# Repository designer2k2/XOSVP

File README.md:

# Xbox Open Source Video Project

XOSVP is an open-source alternative to the Microsoft HD AV Pack. The XOSVP strives to produce the absolute best analog video quality out of your original Xbox.

## Features
- Highest possible quality analog Y/Pb/Pr component video out
    - Impedance matched board traces and cabling from original Xbox
    - High quality video filter + amplifier, [THS7316](https://www.ti.com/lit/ds/symlink/ths7316.pdf)
        - Low pass filter removes high-frequency noise and aberrations from the source signal without harming video frequencies
        - Reconstructs + Amplifies original signal to ensure matching with the Y/Pb/Pr Standards
        - Reduces DAC Imaging effects on the video receiver
- Optical Audio/SPDIF
    - Best possible audio quality from the original Xbox
    - Support Stereo -> 5.1 Surround Sound
    - Cheap, high-quality optical DAC's easy to source on Amazon/Ebay for those without stereo systems

## More Details
[Check out my in-depth blog post on the XOSVP detailing its construction, evolution, and comparison images.](https://blog.dtho.mp/2018/12/15/xosvp-intro/)

## Designs
- [**Schematics**](/xosvp.pdf)
- [**PCB**](/pcb.png)
- [**BOM**](/bom.csv)
- [**Enclosure**](/enclosure.obj)

All designs are produced with KiCAD 5. This includes all schematic sources, designed footprints, and PCB layout.

## Enclosure

Also within this repo is a 3D printable enclosure for the XOSVP. It is designed for friction fit so please ensure your 3D printer is calibrated properly before printing. All files were exported with Millimeter scale.

The enclosure was designed with Tinkercad, and you can view this design [HERE](https://www.tinkercad.com/things/6Rlx4JstT6S-xosvp-enclosure-v3).

## License
I want high-quality analog video from the original Xbox to be available to everyone, which is why I open sourced this project. Everything within this repo is covered by [CERN Open Hardware License v1.2](/LICENSE).

## Contributing
If you have any suggested changes/improvements, please feel free to create an issue or a PR. They will be happily accepted!

# Build Instructions

## Kit
The Following image contains all the parts in the BOM/XOSVP DIY Kit:

## PCB Installation

The parts are placed on the board in the following configuration

The 3D Printed enclosure is designed for a friction fit, so it is very important that the Y/Pb/Pr jack and VGA connector are completely flush to the PCB like in the following image:

## AVIP to XOSVP

To make the cable that connects the Xbox to the AVIP, you will need to splice the included AVIP connector with the included VGA cable.

Creating this cable is a rather involved process, and you want to get it right, so I created the following video tutorial to document the process I follow when making them.

[**YouTube Video Tutorial**](https://www.youtube.com/watch?v=ltjp-2m_H6U)

The following pinouts are provided for extra detail and are intended to be used alongside the video tutorial.

This splice must follow the following pinout guide

Each of the colored AVIP pins must be connected so that they match the following pinout of the VGA cable. The only exception is the `AVIP JMP 1` and `AVIP JMP 2` pins. These need to be jumped together on the top + bottom of the AVIP connector.

## Changes

The PCB is been modified to fit also alternative toslink adapters. In this case Cliff OTJ-8

A label to identify the cable order is now in place (in case no color coded connectors are used)

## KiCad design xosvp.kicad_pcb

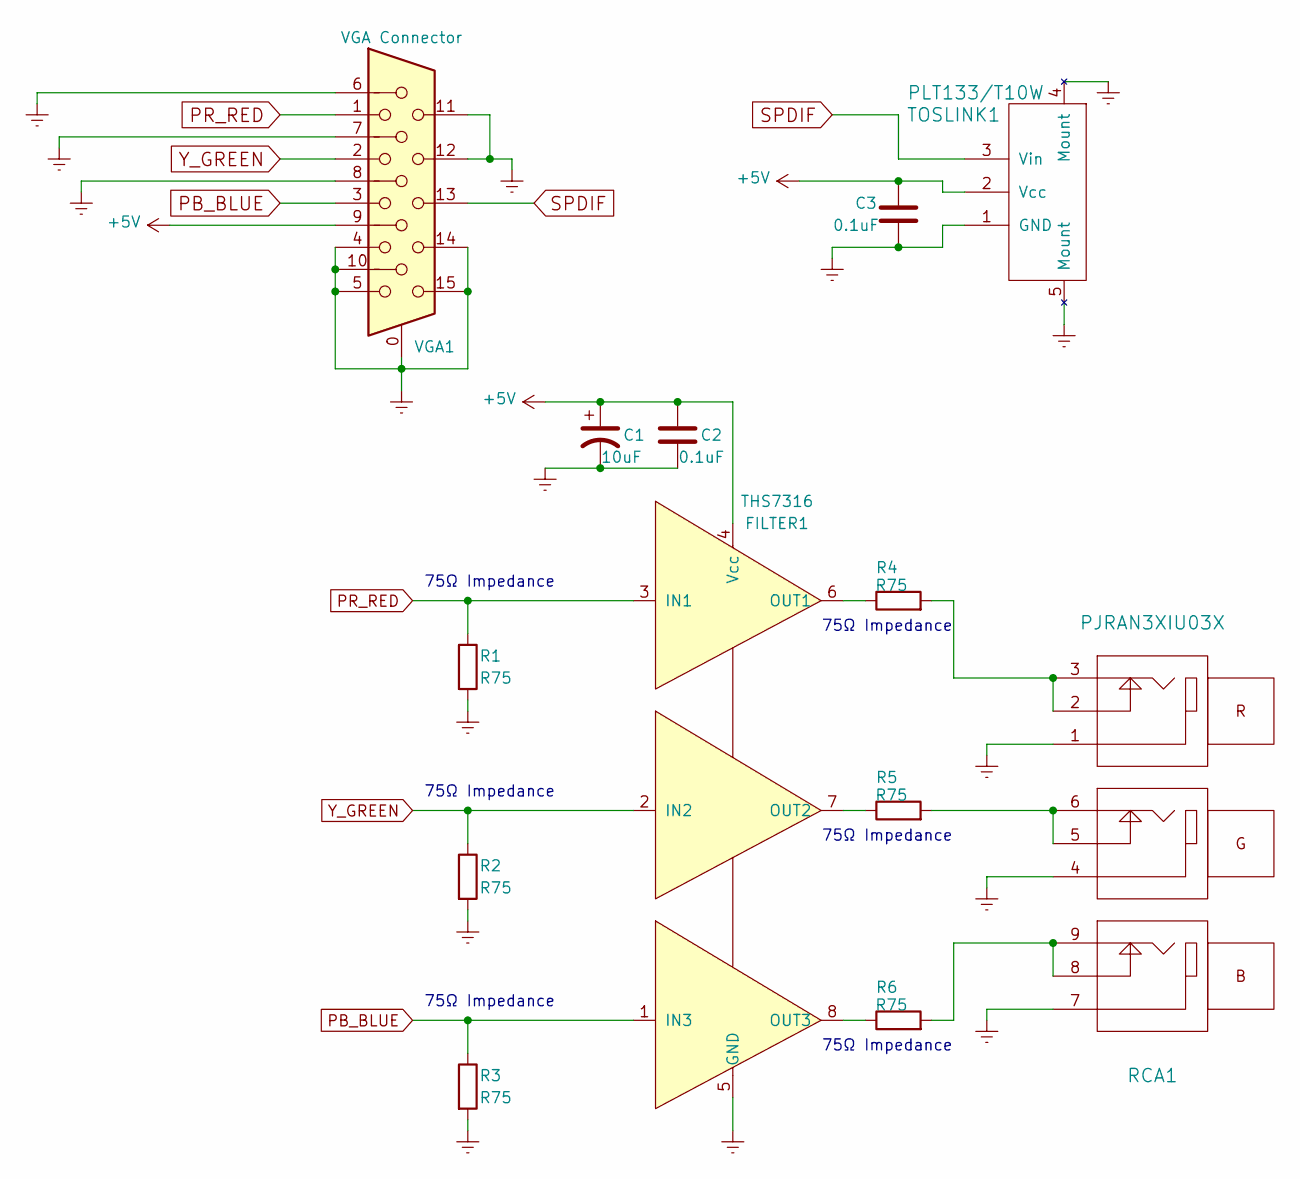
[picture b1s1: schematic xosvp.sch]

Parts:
C1: 10uF; CP_Elec_4x5.8
C2, C3: 0.1uF; C_0805_2012Metric
FILTER1: THS7316
R1, R2, R3, R4, R5, R6: R75; R_0805_2012Metric
RCA1: PJRAN3XIU03X; PJRAN3X1U
TOSLINK1: PLT133/T10W; PLT133
VGA1: VGA Connector; AHDF15A

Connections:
+5V: C1.1, C2.1, C3.1, FILTER1.4 (Vcc), TOSLINK1.2 (Vcc), VGA1.9
Earth: C1.2, C2.2, C3.2, FILTER1.5 (GND), R1.2, R2.2, R3.2, RCA1.1, RCA1.4, RCA1.7, TOSLINK1.1 (GND), TOSLINK1.4 (Mount), TOSLINK1.5 (Mount), VGA1.0, VGA1.4, VGA1.5, VGA1.6, VGA1.7, VGA1.8, VGA1.10, VGA1.11, VGA1.12, VGA1.14, VGA1.15
unnamed: FILTER1.6 (OUT1), R4.1
unnamed: FILTER1.7 (OUT2), R5.1
unnamed: FILTER1.8 (OUT3), R6.1
unnamed: R4.2, RCA1.2, RCA1.3
unnamed: R5.2, RCA1.5, RCA1.6
unnamed: R6.2, RCA1.8, RCA1.9
PB_BLUE: FILTER1.1 (IN3), R3.1, VGA1.3
PR_RED: FILTER1.3 (IN1), R1.1, VGA1.1
SPDIF: TOSLINK1.3 (Vin), VGA1.13
Y_GREEN: FILTER1.2 (IN2), R2.1, VGA1.2

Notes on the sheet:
75Ω Impedance

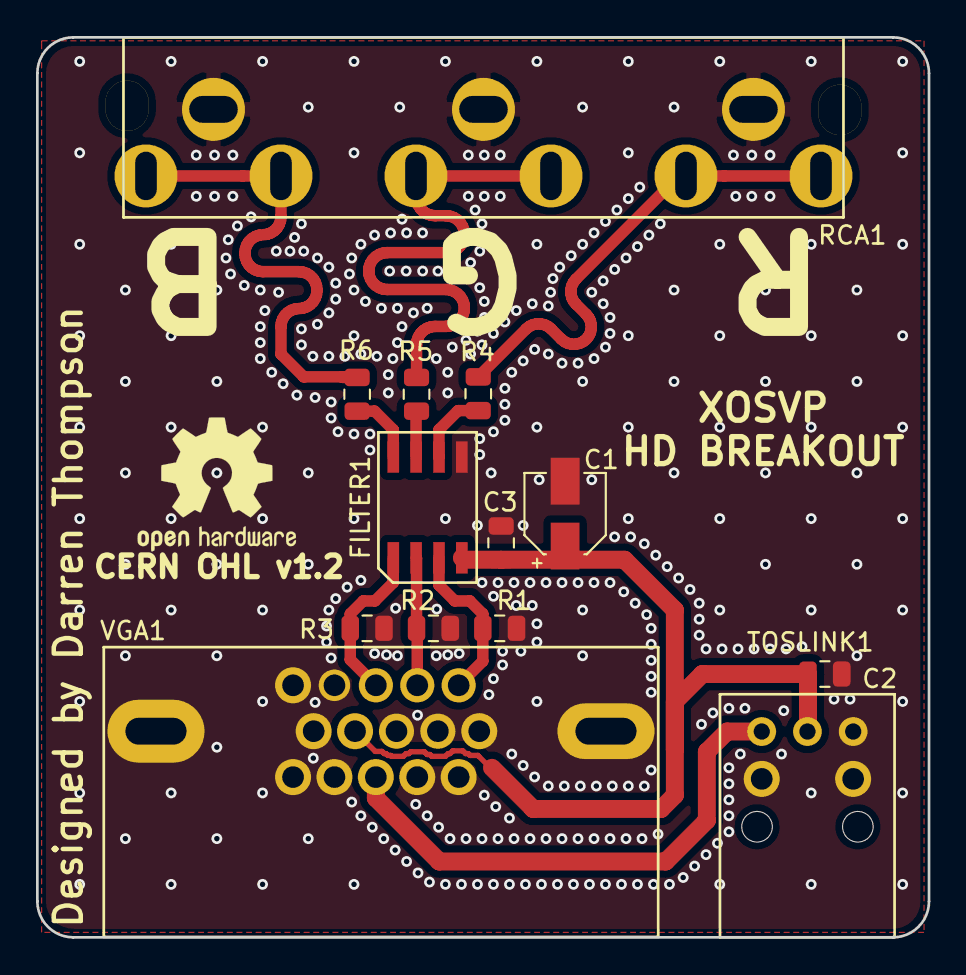
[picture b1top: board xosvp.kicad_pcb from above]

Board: 2 copper layers, 49.5 x 50.0 mm, 13 parts (0 on the bottom side), 12 nets.

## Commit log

2020-07-07 pcb changes
    - toslink footprint variation
    - connector labeling
    - round edges
    - schematic header
2020-07-07 image add/rework
    add image from changes
    compress existing images (tinypng.com)
2020-07-07 document changes
    add image and text on change to pcb
2020-07-07 add images
    build new assembly
    (and minified existing images)
2020-07-07 add assembly image
2020-08-29 add source for Avip connector

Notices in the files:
xosvp.kicad_pcb:
CERN OHL v1.2
